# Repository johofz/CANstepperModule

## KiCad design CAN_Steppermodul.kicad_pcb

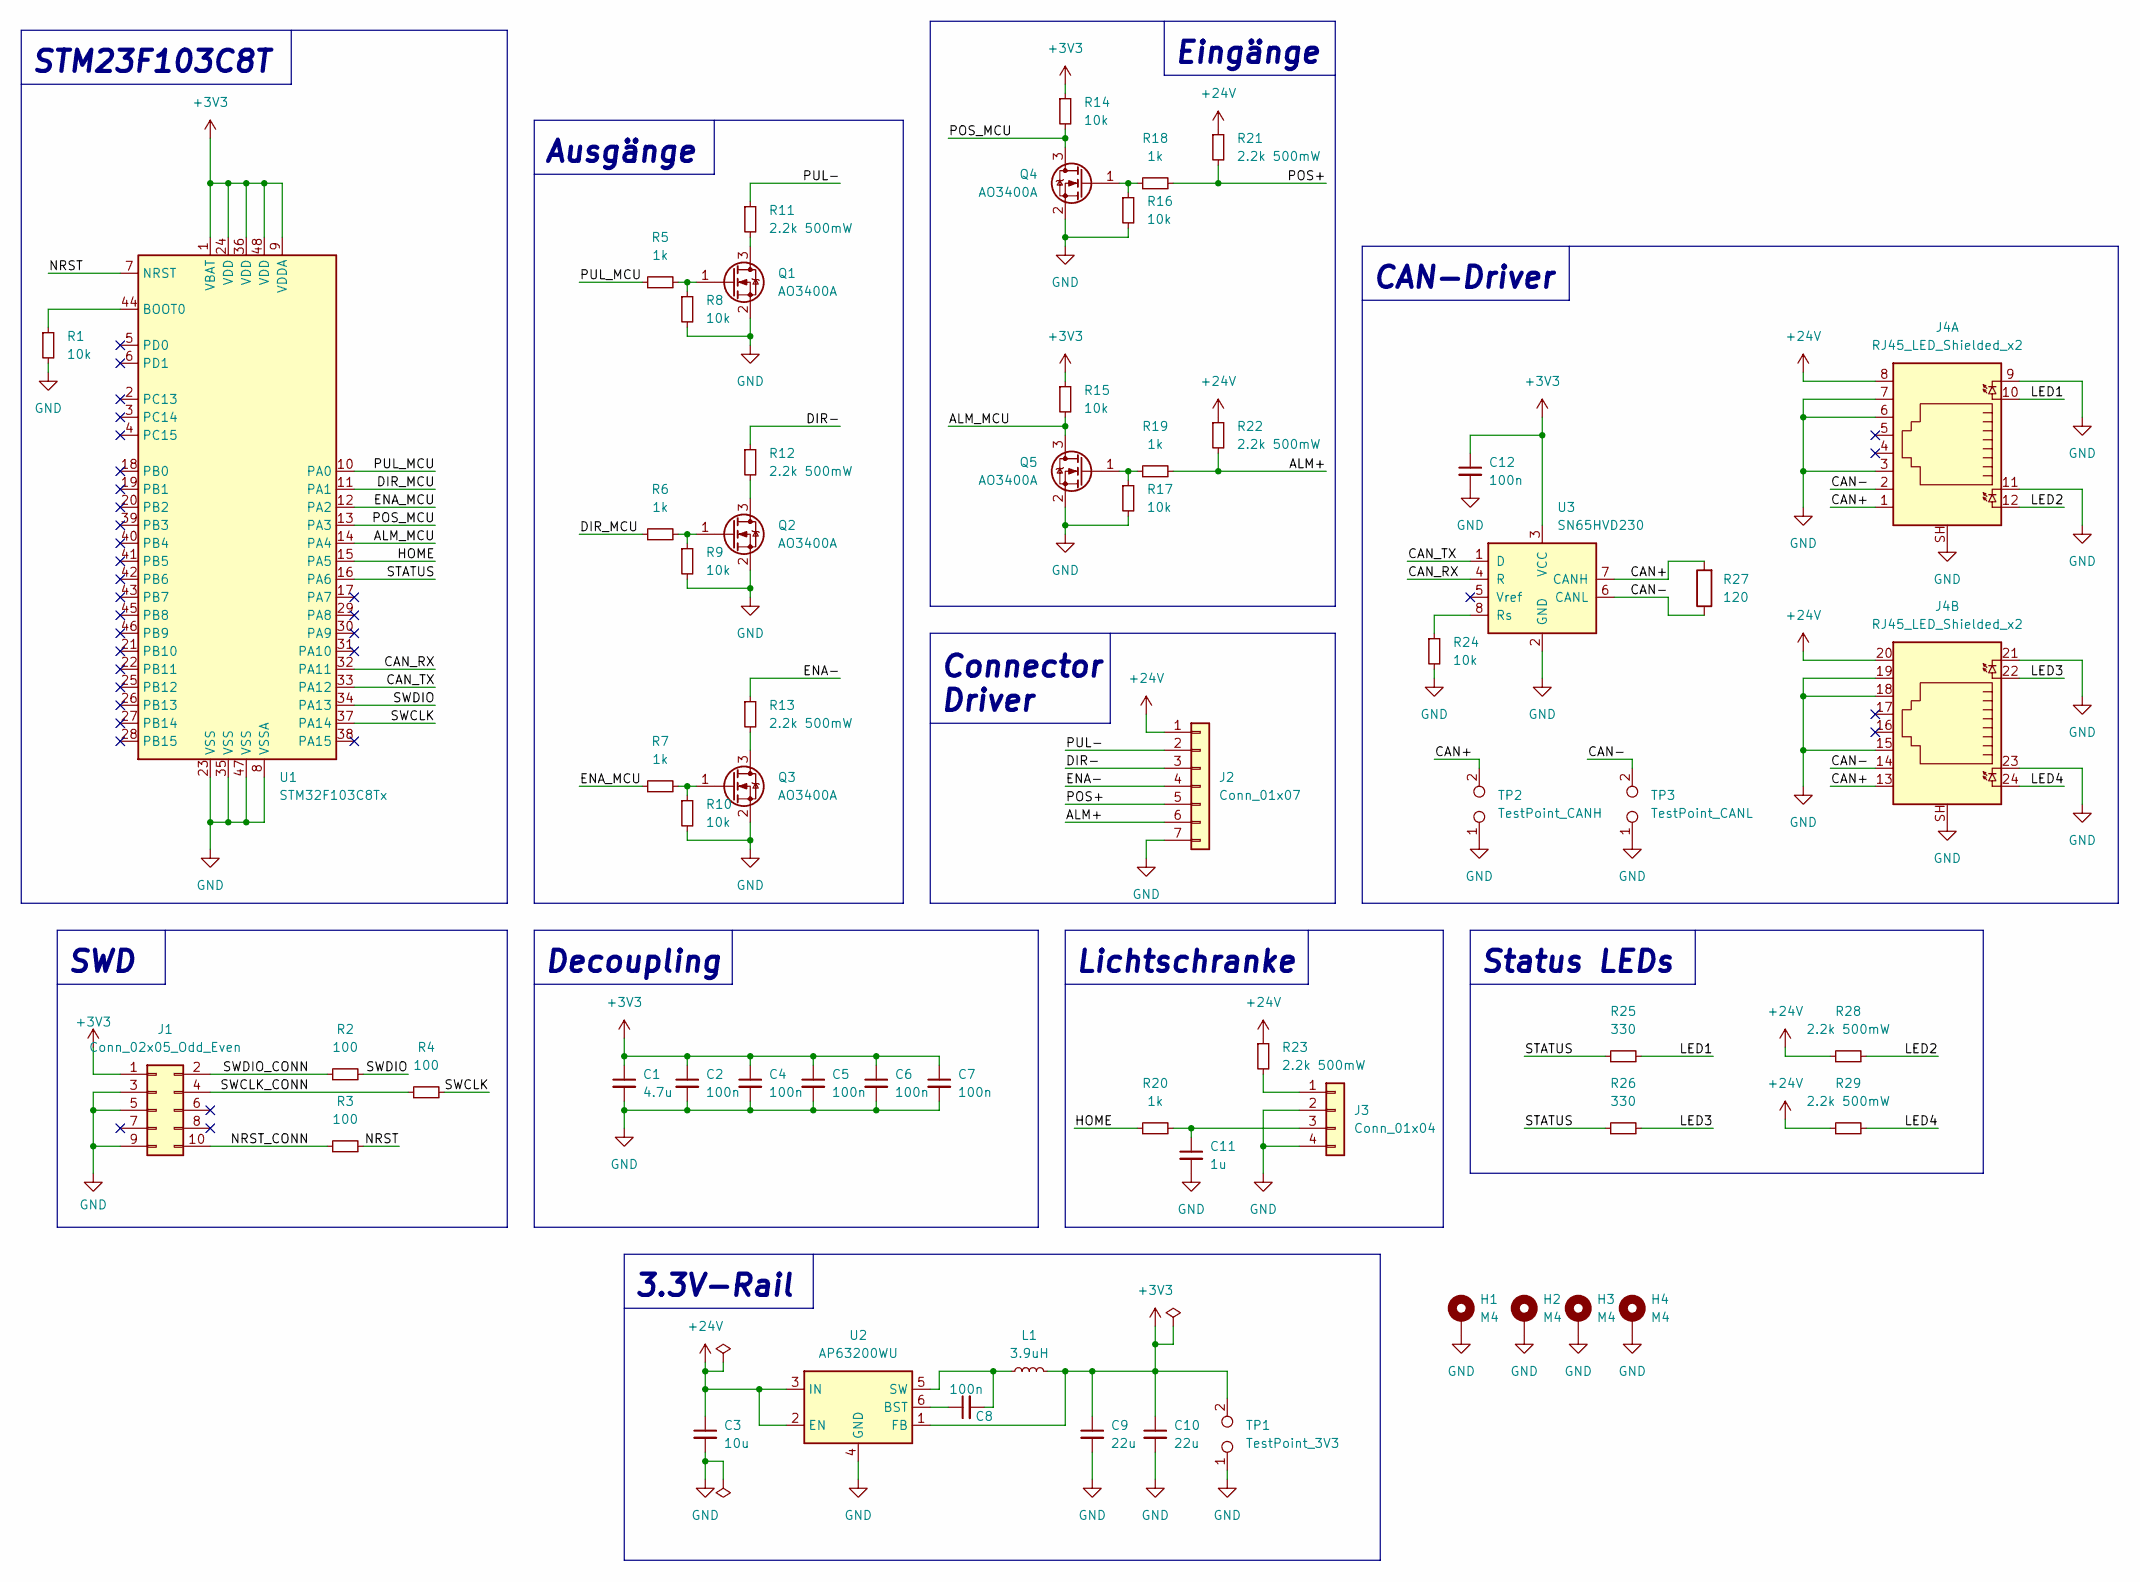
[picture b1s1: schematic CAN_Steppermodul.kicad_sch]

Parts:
C1: 4.7u; C_0603_1608Metric
C2, C4, C5, C6, C7, C8, C12: 100n; C_0402_1005Metric
C3: 10u; C_0805_2012Metric
C9, C10: 22u; C_1206_3216Metric
C11: 1u; C_0402_1005Metric
H1, H2, H3, H4: M4; MountingHole_4.3mm_M4_Pad_Via
J1: Conn_02x05_Odd_Even; PinHeader_2x05_P1.27mm_Vertical_SMD
J2: Conn_01x07; 61900711121
J3: Conn_01x04; 61900411121
J4: RJ45_LED_Shielded_x2; RJ45_Amphenol_RJHSE538X-02
L1: 3.9uH; L_Abracon_ASPI-3012S
Q1, Q2, Q3, Q4, Q5: AO3400A; SOT-23
R1, R8, R9, R10, R14, R15, R16, R17, R24: 10k; R_0402_1005Metric
R2, R3, R4: 100; R_0402_1005Metric
R5, R6, R7, R18, R19, R20: 1k; R_0402_1005Metric
R11, R12, R13, R21, R22, R23, R28, R29: 2.2k 500mW; R_0805_2012Metric
R25, R26: 330; R_0402_1005Metric
R27: 120; R_0402_1005Metric
TP1: TestPoint_3V3; TestPoint_2Pads_Pitch2.54mm_Drill0.8mm
TP2: TestPoint_CANH; TestPoint_2Pads_Pitch2.54mm_Drill0.8mm
TP3: TestPoint_CANL; TestPoint_2Pads_Pitch2.54mm_Drill0.8mm
U1: STM32F103C8Tx; LQFP-48_7x7mm_P0.5mm
U2: AP63200WU; TSOT-23-6
U3: SN65HVD230; SOIC-8_3.9x4.9mm_P1.27mm

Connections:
+3V3: C1.1, C2.1, C4.1, C5.1, C6.1, C7.1, C9.1, C10.1, C12.1, J1.1, L1.2, R14.1, R15.1, TP1.2, U1.1 (VBAT), U1.9 (VDDA), U1.24 (VDD), U1.36 (VDD), U1.48 (VDD), U2.1 (FB), U3.3 (VCC)
+24V: C3.1, J2.1, J4.8, J4.20, R21.1, R22.1, R23.1, R28.1, R29.1, U2.2 (EN), U2.3 (IN)
/ALM+: J2.6, R19.2, R22.2
/ALM_MCU: Q5.3 (D), R15.2, U1.14 (PA4)
/CAN+: J4.1, J4.13, R27.2, TP2.2, U3.7 (CANH)
/CAN-: J4.2, J4.14, R27.1, TP3.2, U3.6 (CANL)
/CAN_RX: U1.32 (PA11), U3.4 (R)
/CAN_TX: U1.33 (PA12), U3.1 (D)
/DIR-: J2.3, R12.1
/DIR_MCU: R6.1, U1.11 (PA1)
/ENA-: J2.4, R13.1
/ENA_MCU: R7.1, U1.12 (PA2)
/HOME: R20.1, U1.15 (PA5)
/LED1: J4.10, R25.2
/LED2: J4.12, R28.2
/LED3: J4.22, R26.2
/LED4: J4.24, R29.2
/NRST: R3.2, U1.7 (NRST)
/NRST_CONN: J1.10, R3.1
/POS+: J2.5, R18.2, R21.2
/POS_MCU: Q4.3 (D), R14.2, U1.13 (PA3)
/PUL-: J2.2, R11.1
/PUL_MCU: R5.1, U1.10 (PA0)
/STATUS: R25.1, R26.1, U1.16 (PA6)
/SWCLK: R4.2, U1.37 (PA14)
/SWCLK_CONN: J1.4, R4.1
/SWDIO: R2.2, U1.34 (PA13)
/SWDIO_CONN: J1.2, R2.1
GND: C1.2, C2.2, C3.2, C4.2, C5.2, C6.2, C7.2, C9.2, C10.2, C11.2, C12.2, H1.1, H2.1, H3.1, H4.1, J1.3, J1.5, J1.9, J2.7, J3.2, J3.4, J4.3, J4.6, J4.7, J4.9, J4.11, J4.15, J4.18, J4.19, J4.21, J4.23, J4.SH, Q1.2 (S), Q2.2 (S), Q3.2 (S), Q4.2 (S), Q5.2 (S), R1.2, R8.2, R9.2, R10.2, R16.2, R17.2, R24.2, TP1.1, TP2.1, TP3.1, U1.8 (VSSA), U1.23 (VSS), U1.35 (VSS), U1.47 (VSS), U2.4 (GND), U3.2 (GND)
unnamed: C8.1, U2.6 (BST)
unnamed: C8.2, L1.1, U2.5 (SW)
unnamed: C11.1, J3.3, R20.2
unnamed: J3.1, R23.2
unnamed: Q1.1 (G), R5.2, R8.1
unnamed: Q1.3 (D), R11.2
unnamed: Q2.1 (G), R6.2, R9.1
unnamed: Q2.3 (D), R12.2
unnamed: Q3.1 (G), R7.2, R10.1
unnamed: Q3.3 (D), R13.2
unnamed: Q4.1 (G), R16.1, R18.1
unnamed: Q5.1 (G), R17.1, R19.1
unnamed: R1.1, U1.44 (BOOT0)
unnamed: R24.1, U3.8 (Rs)

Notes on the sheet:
Eingänge
Lichtschranke
SWD
Connector Driver
CAN-Driver
Ausgänge
3.3V-Rail
STM23F103C8T
Decoupling
Status LEDs

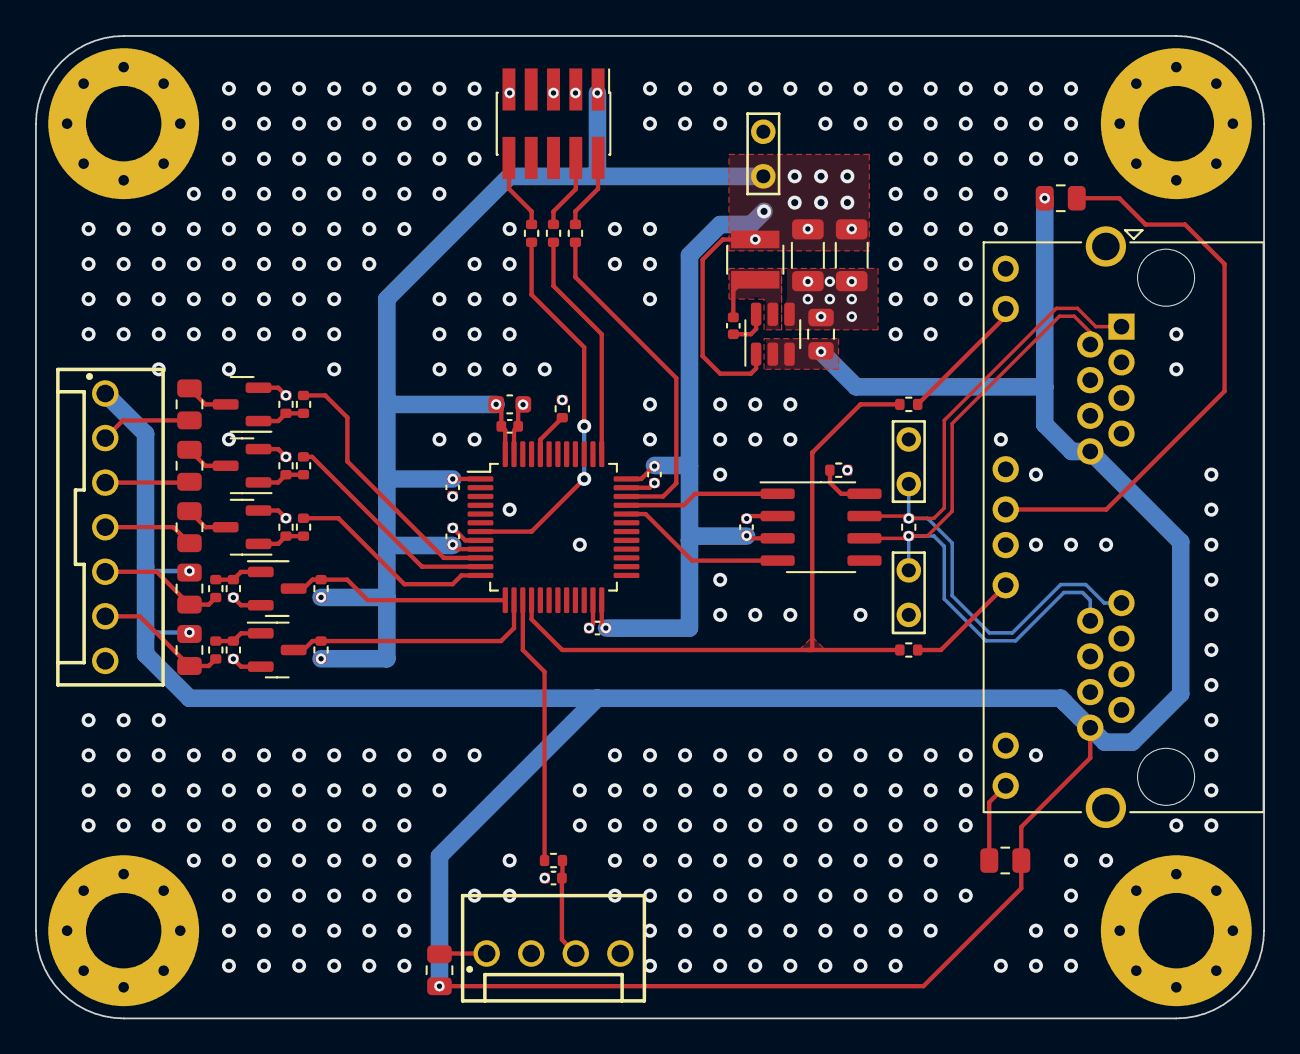
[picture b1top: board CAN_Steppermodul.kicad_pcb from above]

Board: 4 copper layers, 70.0 x 56.0 mm, 61 parts (0 on the bottom side), 43 nets.

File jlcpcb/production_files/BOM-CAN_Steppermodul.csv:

Comment,Designator,Footprint,LCSC
10k,"R1,R10,R14,R15,R16,R17,R24,R8,R9",R_0402_1005Metric,C11616
1k,"R18,R19,R20,R5,R6,R7",R_0402_1005Metric,C11702
SN65HVD230,U3,SOIC-8_3.9x4.9mm_P1.27mm,C12084
22u,"C10,C9",C_1206_3216Metric,C12891
Conn_02x05_Odd_Even,J1,PinHeader_2x05_P1.27mm_Vertical_SMD,C150517
4.7u,C1,C_0603_1608Metric,C19666
AP63200WU,U2,TSOT-23-6,C2071868
AO3400A,"Q1,Q2,Q3,Q4,Q5",SOT-23,C20917
100,"R2,R3,R4",R_0402_1005Metric,C25076
120,R27,R_0402_1005Metric,C25079
330,"R25,R26",R_0402_1005Metric,C25104
100n,"C12,C2,C4,C5,C6,C7,C8",C_0402_1005Metric,C307331
3.9uH,L1,L_Abracon_ASPI-3012S,C431700
10u,C3,C_0805_2012Metric,C440198
2.2k 500mW,"R11,R12,R13,R21,R22,R23,R28,R29",R_0805_2012Metric,C441982
1u,C11,C_0402_1005Metric,C52923
RJ45_LED_Shielded_x2,J4,RJ45_Amphenol_RJHSE538X-02,C86581
STM32F103C8Tx,U1,LQFP-48_7x7mm_P0.5mm,C8734

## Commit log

2024-05-23 Update auf Kicad 7
